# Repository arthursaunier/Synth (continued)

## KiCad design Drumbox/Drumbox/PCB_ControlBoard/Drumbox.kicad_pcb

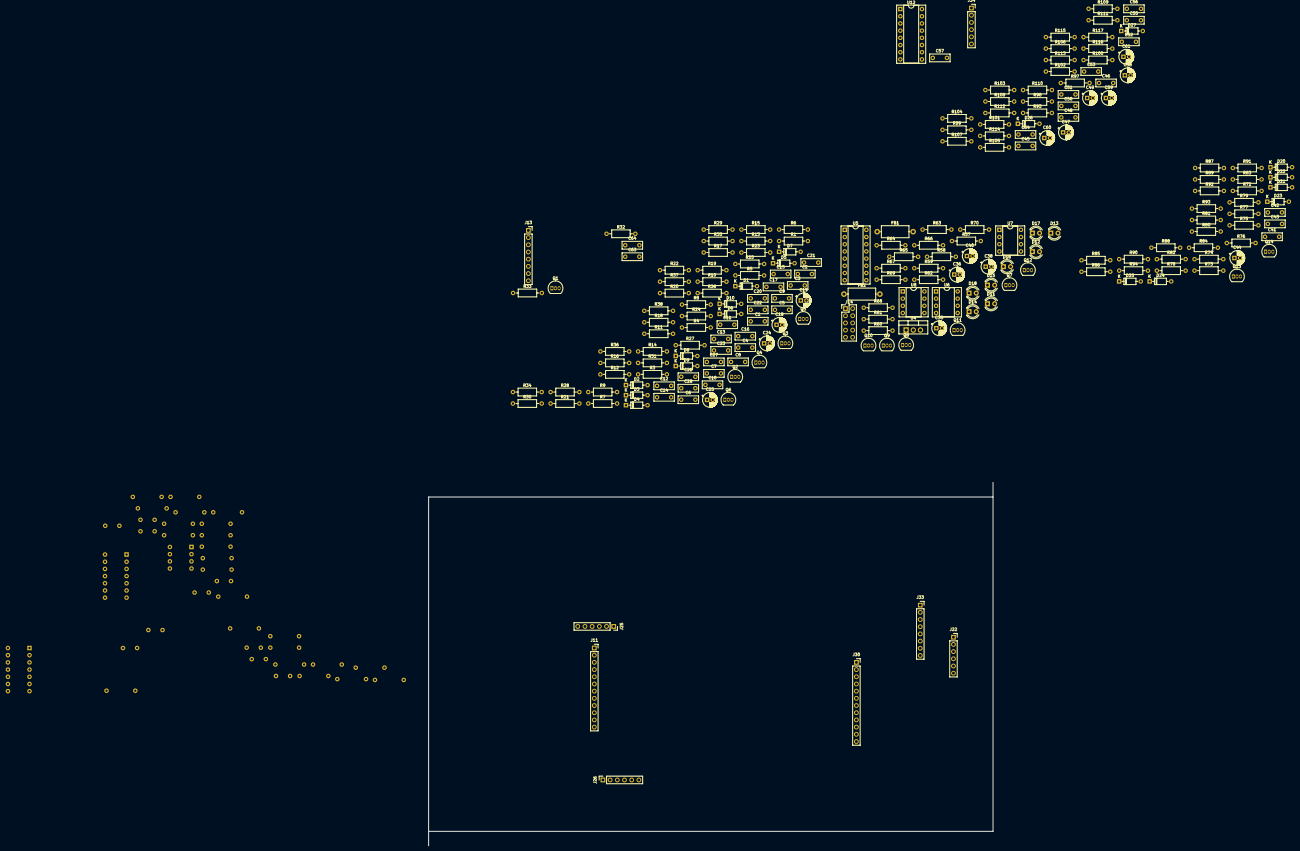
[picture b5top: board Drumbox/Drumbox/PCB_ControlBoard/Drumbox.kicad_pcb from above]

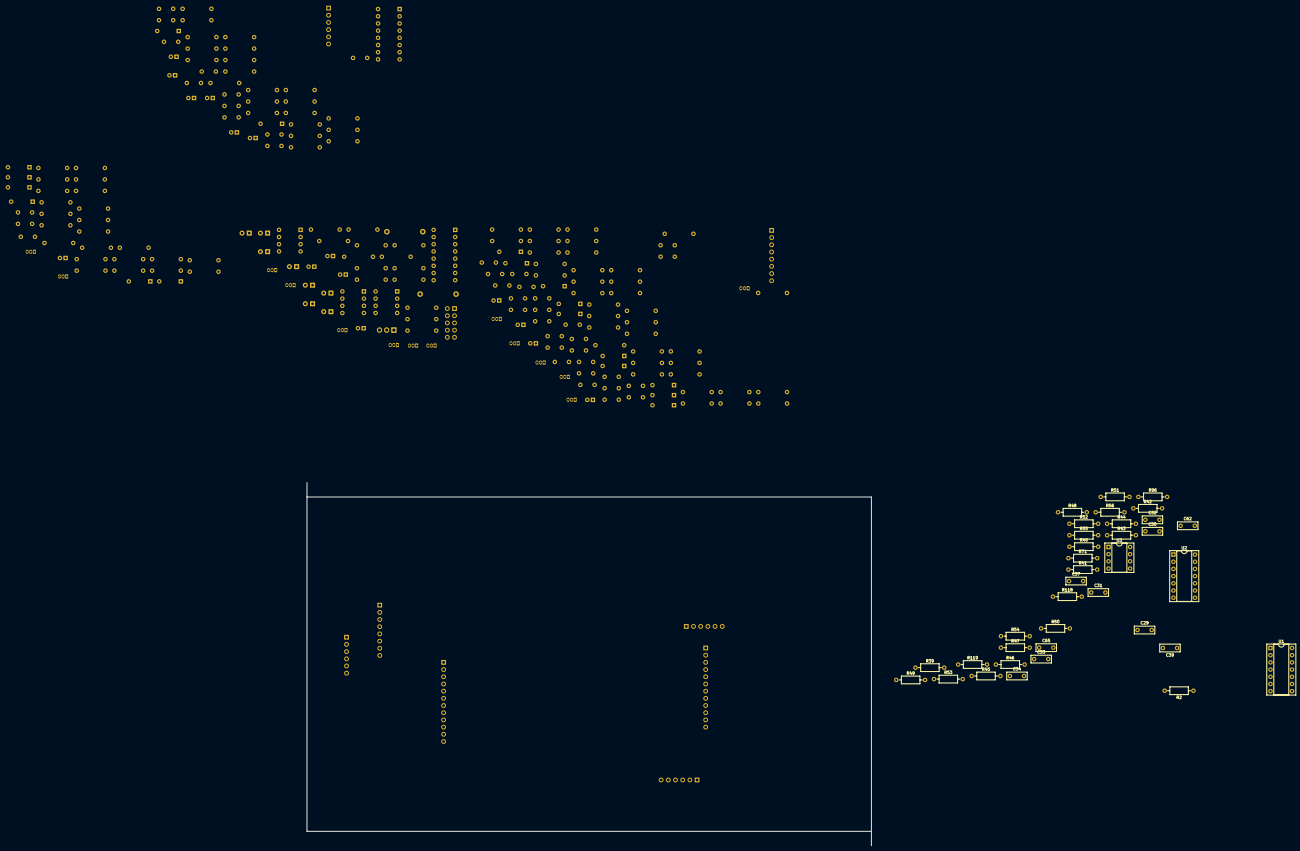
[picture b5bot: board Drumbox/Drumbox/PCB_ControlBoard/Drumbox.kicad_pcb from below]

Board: 2 copper layers, 199.4 x 128.3 mm, 244 parts (36 on the bottom side), 177 nets, no tracks yet.

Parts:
C1, C4: 150nF; C_Disc_D7.0mm_W2.5mm_P5.00mm
C2, C3: 47nF; C_Disc_D7.0mm_W2.5mm_P5.00mm
C5, C8: 33nF; C_Disc_D7.0mm_W2.5mm_P5.00mm
C6, C7, C27: 10nF; C_Disc_D7.0mm_W2.5mm_P5.00mm
C9, C12: 39nF; C_Disc_D7.0mm_W2.5mm_P5.00mm
C10, C11: 12nF; C_Disc_D7.0mm_W2.5mm_P5.00mm
C13: 4.7nF; C_Disc_D7.0mm_W2.5mm_P5.00mm
C14, C15: 1.5nF; C_Disc_D7.0mm_W2.5mm_P5.00mm
C16: 56nF; C_Disc_D7.0mm_W2.5mm_P5.00mm
C17, C21, C23: 0.1µF; C_Disc_D7.0mm_W2.5mm_P5.00mm
C18, C19, C24, C25, C44, C49, C59, C60: 10µF; CP_Radial_D5.0mm_P2.00mm
C20, C26: 1µF; C_Disc_D7.0mm_W2.5mm_P5.00mm
C22: 50nF; C_Disc_D7.0mm_W2.5mm_P5.00mm
C28: 680pF; C_Disc_D7.0mm_W2.5mm_P5.00mm
C29, C30, C31, C32, C33, C34: 10µF; C_Disc_D7.0mm_W2.5mm_P5.00mm
C35, C36, C38: 10µ; CP_Radial_D5.0mm_P2.00mm
C37, C39, C62, C63, C64, C65: .1µF; C_Disc_D7.0mm_W2.5mm_P5.00mm
C40: 100n; CP_Radial_D5.0mm_P2.00mm
C41, C42, C43: 1nF; C_Disc_D7.0mm_W2.5mm_P5.00mm
C45, C55: 22nF; C_Disc_D7.0mm_W2.5mm_P5.00mm
C46: 500pF; C_Disc_D7.0mm_W2.5mm_P5.00mm
C47: 2.2µF; CP_Radial_D5.0mm_P2.00mm
C48, C50, C51, C54, C56: 100nF; C_Disc_D7.0mm_W2.5mm_P5.00mm
C52, C53: 470pF; C_Disc_D7.0mm_W2.5mm_P5.00mm
C57: 2.2nF; C_Disc_D7.0mm_W2.5mm_P5.00mm
C58, C61: 4.7µF; CP_Radial_D5.0mm_P2.00mm
D1, D2, D3, D4, D5, D6, D7, D8, D9, D10, D20, D21, D22, D23, D24, D25: 1N4148; D_DO-35_SOD27_P7.62mm_Horizontal
D11: LED5; LED_D4.0mm
D12: LED1; LED_D4.0mm
D13: LED6; LED_D4.0mm
D14: LED2; LED_D4.0mm
D15: LED3; LED_D4.0mm
D16: LED-5V; LED_D4.0mm
D17: LED-9V; LED_D4.0mm
D18: LED4; LED_D4.0mm
D26, D27: 1N914; D_DO-35_SOD27_P7.62mm_Horizontal
FB1, FB2: 10R; L_Axial_L9.5mm_D4.0mm_P12.70mm_Horizontal_Fastron_SMCC
J11, J30: Conn_01x12_Female; PinSocket_1x12_P2.54mm_Vertical
J13, J33: Conn_01x08_Female; PinSocket_1x08_P2.54mm_Vertical
J14: Power Input; PinHeader_2x05_P2.54mm_Vertical
J22, J25, J26, J34: Conn_01x06_Female; PinSocket_1x06_P2.54mm_Vertical
Q1, Q2, Q3, Q4, Q5, Q6: BC546; TO-92_Inline
Q7, Q8, Q9, Q10, Q11, Q12: 2N3904; TO-92_Inline
Q13, Q14: BC559; TO-92_Inline
R1, R8, R15, R22: 12k; R_Axial_DIN0207_L6.3mm_D2.5mm_P10.16mm_Horizontal
R2, R29, R32, R36, R39, R47, R49, R50, R51, R55, R56: 1M; R_Axial_DIN0207_L6.3mm_D2.5mm_P10.16mm_Horizontal
R3, R10, R17, R24: 27k; R_Axial_DIN0207_L6.3mm_D2.5mm_P10.16mm_Horizontal
R4, R11, R16, R18, R25, R34, R57, R58, R61, R62, R65, R68: 47k; R_Axial_DIN0207_L6.3mm_D2.5mm_P10.16mm_Horizontal
R5, R6, R12, R13, R19, R20, R26, R27: 68k; R_Axial_DIN0207_L6.3mm_D2.5mm_P10.16mm_Horizontal
R7, R14, R21, R28, R97: 150k; R_Axial_DIN0207_L6.3mm_D2.5mm_P10.16mm_Horizontal
R9, R23, R33, R35: 4k7; R_Axial_DIN0207_L6.3mm_D2.5mm_P10.16mm_Horizontal
R30, R37: 100; R_Axial_DIN0207_L6.3mm_D2.5mm_P10.16mm_Horizontal
R31, R38, R86: 33k; R_Axial_DIN0207_L6.3mm_D2.5mm_P10.16mm_Horizontal
R40, R41, R52, R89, R104, R107, R108, R109, R116: 10k; R_Axial_DIN0207_L6.3mm_D2.5mm_P10.16mm_Horizontal
R42, R53, R71: 6.8k; R_Axial_DIN0207_L6.3mm_D2.5mm_P10.16mm_Horizontal
R43, R44, R46, R48, R73, R76, R77, R81, R85, R88, R96, R98, R99, R101, R112, R113, R115, R118, R119: 100k; R_Axial_DIN0207_L6.3mm_D2.5mm_P10.16mm_Horizontal
R45, R54: 390k; R_Axial_DIN0207_L6.3mm_D2.5mm_P10.16mm_Horizontal
R59, R60, R63, R64, R66, R69, R70, R75, R79, R92, R117: 2.2k; R_Axial_DIN0207_L6.3mm_D2.5mm_P10.16mm_Horizontal
R67: 330; R_Axial_DIN0207_L6.3mm_D2.5mm_P10.16mm_Horizontal
R72, R74, R82, R84, R100: 470; R_Axial_DIN0207_L6.3mm_D2.5mm_P10.16mm_Horizontal
R78, R93, R94, R102, R110: 1k; R_Axial_DIN0207_L6.3mm_D2.5mm_P10.16mm_Horizontal
R80, R90: 1.8k; R_Axial_DIN0207_L6.3mm_D2.5mm_P10.16mm_Horizontal
R83: 82k; R_Axial_DIN0207_L6.3mm_D2.5mm_P10.16mm_Horizontal
R87: 56k; R_Axial_DIN0207_L6.3mm_D2.5mm_P10.16mm_Horizontal
R91: 3.3k; R_Axial_DIN0207_L6.3mm_D2.5mm_P10.16mm_Horizontal
R95: 22k; R_Axial_DIN0207_L6.3mm_D2.5mm_P10.16mm_Horizontal
R103: 30k; R_Axial_DIN0207_L6.3mm_D2.5mm_P10.16mm_Horizontal
R105, R106, R111, R114: 15k; R_Axial_DIN0207_L6.3mm_D2.5mm_P10.16mm_Horizontal
U1: 4011; DIP-14_W7.62mm_Socket
U2: TL074; DIP-14_W7.62mm_Socket
U3, U6, U7, U8: TL072; DIP-8_W7.62mm_Socket
U4: L7805; TO-220-3_Vertical
U5: LM13700; DIP-16_W7.62mm_Socket
U12: PT2399; DIP-16_W7.62mm_Socket

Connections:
+5V: C40.1, R67.1, U4.3, U12.1
+12V: C35.1, C38.1, FB1.1, J22.2, J30.2, R23.1, R29.1, R35.1, R36.1, R59.1, R60.1, R63.1, R64.1, R66.1, R69.1, R70.1, R86.2, R97.1, U1.14, U2.4, U3.8, U4.1, U5.11, U6.8, U7.8, U8.8
-12V: C36.2, FB2.1, J30.5, R77.1, R80.1, R87.1, R90.1, U2.11, U3.4, U5.6, U6.4, U7.4, U8.4
CutCV: J30.11, R83.2
Cutoff: J30.10, R85.2
DEIn1: J11.6, R7.1
DEIn2: J11.5, R14.1
DEIn3: J11.4, R21.1
DEIn4: J11.3, R28.1
DEIn5: C4.2, C8.2, C12.2, C16.2, C17.2, C19.2, C21.1, C23.2, C25.2, C27.1, C35.2, C36.1, C38.2, C40.2, C46.2, C48.2, C49.1, C50.2, C55.2, C57.2, D5.2, D8.2, D11.1, D12.1, D13.1, D14.1, D15.1, D16.1, D17.1, D18.1, J11.1, J11.2, J13.1, J13.2, J13.3, J14.3, J14.4, J14.5, J14.6, J14.7, J14.8, J22.1, J22.6, J30.1, J30.3, J30.4, J30.12, J34.1, Q2.3, Q3.3, Q5.3, Q6.3, Q13.2, R1.2, R2.2, R4.1, R8.2, R9.2, R11.1, R15.2, R18.1, R22.2, R25.1, R32.2, R33.2, R39.2, R40.2, R41.2, R42.2, R49.2, R50.2, R51.2, R52.2, R53.2, R71.2, R72.1, R74.1, R79.1, R82.1, R84.1, R92.1, R98.2, R100.2, R109.1, R113.2, R117.2, U1.7, U4.2, U6.5, U8.3, U8.5, U12.3, U12.4
DEOut1: C3.2, C37.1, J11.12, R6.1, U1.3
DEOut2: C7.2, C63.1, J11.11, R13.1, U1.4
DEOut3: C11.2, C39.1, J11.10, R20.1, U1.10
DEOut4: C15.2, C64.1, J11.9, R27.1, U1.11
DEOut5: J11.8, R30.2
DEOut6: J11.7, R37.2
FBIn: C61.2, J34.3
FBOut: J34.2, R116.2
Filter: J33.6, R115.2, U8.7
FilterOut: J22.5, R94.1
FxEchoIn: J33.7, R101.1
FxStupidIn: J33.8, R95.1
GainIn: C47.1, D26.2, D27.1, U7.2
GainOut: C51.2, D26.1, D27.2, J33.1, U7.1
Hpass: C43.2, J30.6
In1: C1.1, J26.6, R1.1, R58.1
In2: C5.1, J26.5, R8.1, R62.1
In3: C9.1, J26.4, R15.1, R65.1
In4: C13.1, J26.3, R22.1, R68.1
In5: C18.1, J26.2, R9.1, R57.1
In6: C24.1, J26.1, R33.1, R61.1
LPass: J30.7, R73.1
unnamed: C1.2, R3.1, R4.2
unnamed: C2.1, R5.2, R7.2, U1.1, U1.2
unnamed: C4.1, R5.1, R6.2
unnamed: C5.2, R10.1, R11.2
unnamed: C6.1, R12.2, R14.2, U1.5, U1.6
unnamed: C8.1, R12.1, R13.2
unnamed: C9.2, R17.1, R18.2
unnamed: C10.1, R19.2, R21.2, U1.8, U1.9
unnamed: C12.1, R19.1, R20.2
unnamed: C13.2, R24.1, R25.2
unnamed: C14.1, R26.2, R28.2, U1.12, U1.13
unnamed: C16.1, R26.1, R27.2
unnamed: C17.1, Q1.3, R16.1
unnamed: C18.2, D5.1, D6.2
unnamed: C19.1, D6.1, R30.1, R31.1
unnamed: C20.1, Q2.1, R16.2, R23.2
unnamed: C20.2, C21.2, Q3.2, R29.2
unnamed: C22.1, D7.2, R31.2
unnamed: C23.1, Q4.3, R34.1
unnamed: C24.2, D8.1, D9.2
unnamed: C25.1, D9.1, R37.1, R38.1
unnamed: C26.1, Q5.1, R34.2, R35.2
unnamed: C26.2, C27.2, Q6.2, R36.2
unnamed: C28.1, D10.2, R38.2
unnamed: C29.1, R44.1, U2.8
unnamed: C29.2, R45.2
unnamed: C30.1, R43.1, U2.1
unnamed: C30.2, R46.2
unnamed: C31.1, R48.1, U3.1
unnamed: C31.2, R47.2
unnamed: C32.1, R96.1, U2.7
unnamed: C32.2, R54.2
unnamed: C33.1, R118.1, U2.14
unnamed: C33.2, R55.2
unnamed: C34.1, R119.1, U3.7
unnamed: C34.2, R56.2
unnamed: C37.2, R2.1, U2.3
unnamed: C39.2, R32.1, U2.10
unnamed: C41.1, U5.5, U5.7
unnamed: C41.2, R89.1, R91.2, U6.1
unnamed: C42.1, R78.2, U6.7
unnamed: C42.2, Q14.1, R77.2, U6.6
unnamed: C43.1, U5.10, U5.12
unnamed: C44.1, R93.2, R94.2
unnamed: C44.2, R88.2, R90.2, U5.9
unnamed: C45.1, R97.2, R98.1, R99.1
unnamed: C45.2, R95.2, R117.1
unnamed: C46.1, R99.2, U7.3
unnamed: C47.2, R100.1
unnamed: C48.1, U12.7
unnamed: C49.2, U12.2
unnamed: C50.1, U12.8
unnamed: C52.1, R104.1, U12.16
unnamed: C52.2, C59.1, R105.1, U12.15
unnamed: C53.1, R106.1, R110.1, U12.14
unnamed: C53.2, R107.1, U12.13
unnamed: C54.1, U12.10
unnamed: C54.2, U12.9
unnamed: C56.1, R108.1, U12.12
unnamed: C56.2, U12.11
unnamed: C57.1, R106.2, R107.2, R108.2
unnamed: C58.1, R111.2
unnamed: C58.2, R103.2, R113.1, U8.1
unnamed: C59.2, R114.1
unnamed: C60.1, R110.2
unnamed: C61.1, R104.2, R105.2, R111.1
unnamed: C62.2, R39.1, U3.3
unnamed: C63.2, R49.1, U2.5
unnamed: C64.2, R50.1, U2.12
unnamed: C65.2, R51.1, U3.5
unnamed: D1.2, R3.2
unnamed: D2.2, R10.2
unnamed: D3.2, R17.2
unnamed: D4.2, R24.2
unnamed: D7.1, Q3.1
unnamed: D10.1, Q6.1
unnamed: D11.2, Q7.1
unnamed: D12.2, Q8.1
unnamed: D13.2, Q9.1
unnamed: D14.2, Q10.1
unnamed: D15.2, Q11.1
unnamed: D16.2, R67.2
unnamed: D17.2, R69.2
unnamed: D18.2, Q12.1
unnamed: D20.1, D22.2
unnamed: D20.2, D21.1, R89.2
unnamed: D21.2, D23.1
unnamed: D22.1, D24.2
unnamed: D23.2, D25.1
unnamed: D24.1, D25.2, R91.1, R92.2, U6.2
unnamed: FB1.2, J14.1, J14.2
unnamed: FB2.2, J14.9, J14.10
unnamed: Q1.2, Q2.2
unnamed: Q4.2, Q5.2
unnamed: Q7.2, R57.2
unnamed: Q7.3, R59.2
unnamed: Q8.2, R58.2
unnamed: Q8.3, R60.2
unnamed: Q9.2, R61.2
unnamed: Q9.3, R63.2
unnamed: Q10.2, R62.2
unnamed: Q10.3, R64.2
unnamed: Q11.2, R65.2
unnamed: Q11.3, R66.2
unnamed: Q12.2, R68.2
unnamed: Q12.3, R70.2
unnamed: Q13.1, R75.1
unnamed: Q13.3, Q14.3, R78.1
unnamed: Q14.2, R79.2, R83.1, R85.1
unnamed: R40.1, R44.2, U2.9
unnamed: R41.1, R43.2, U2.2
unnamed: R42.1, R48.2, U3.2
unnamed: R52.1, R96.2, U2.6
unnamed: R72.2, R76.1, U5.4
unnamed: R73.2, R74.2, U5.3
unnamed: R75.2, U5.1, U5.16
unnamed: R76.2, R80.2, R81.1, U5.8
unnamed: R81.2, R84.2, U5.14
unnamed: R82.2, R88.1, U5.13
unnamed: R101.2, R103.1, U8.2
unnamed: R102.2, U12.6
unnamed: R109.2, R112.1, U7.6
unnamed: R114.2, R115.1, U8.6
unnamed: R53.1, R118.2, U2.13
unnamed: R71.1, R119.2, U3.6
O5: C22.2, C62.1
O6: C28.2, C65.1
PI1Out: C2.2, C3.1, D1.1
PIOut2: C6.2, C7.1, D2.1, J13.7
PIOut3: C10.2, C11.1, D3.1, J13.6
PIOut4: C14.2, C15.1, D4.1, J13.5
ResIn: J30.9, R93.1
ResOut: J30.8, U6.3
TimeOut: J34.6, R102.1
ToneEchoIn: C60.2, J34.5
ToneEchoOut: J34.4, R116.1
ToneIN: C51.1, J33.4
ToneOUT: C55.1, J33.3, U7.5
Vol1: J25.6, R46.1
Vol2: J25.5, R54.1
Vol3: J25.4, R45.1
Vol4: J25.3, R55.1
Vol5: J25.2, R47.1
Vol6: J25.1, R56.1
VolOut: J33.2, R112.2, U7.7
